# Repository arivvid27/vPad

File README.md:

# vPad

### Note:
> This is probably something I'm
> gonna reiterate on a lot
> whenever I have time, so, it's a
> WIP

## Current Features:
- Mechanical Switches (MX Basic | Macros)
- Two NeoPixels (Ambience)
- Encoder + Switch (Volume/Brightness Control/Mute/Unmute/More Macros)

## What's Holding it Together;
- Not Duct-Tape this time
- KMK Firmware
- Circuit Python

## WIP Stuff:
- Custom Software to work with this pad
- Mini OLED Screen
- Better Ambient Lighting (Underglow, Keycaps)

## Future Stuff:
- Expand to full Keyboards
- Mice?
- Definitely a Better case 😭
- More Switches (Imma find those push things where they stay on until you push them again)

## Challenges:
I was quite a bit stumped on how to use KiCad. The tutorial helped a ton. I also have never imported anything into F360... so it took me a while to figure that out.
Overall, I think I learned a lot from this, and I will continue to make PCBs now that I know how to. :)

## Schematics:

## PCB:

## (Attempt at) Case:

## BOM
- 2x SK6812MINI
- 4x Cherry MX Standard Switches (Anything Tactile)
- 1x EC11 Rotary Encoder
- 1x XIAO RP2040 DIP

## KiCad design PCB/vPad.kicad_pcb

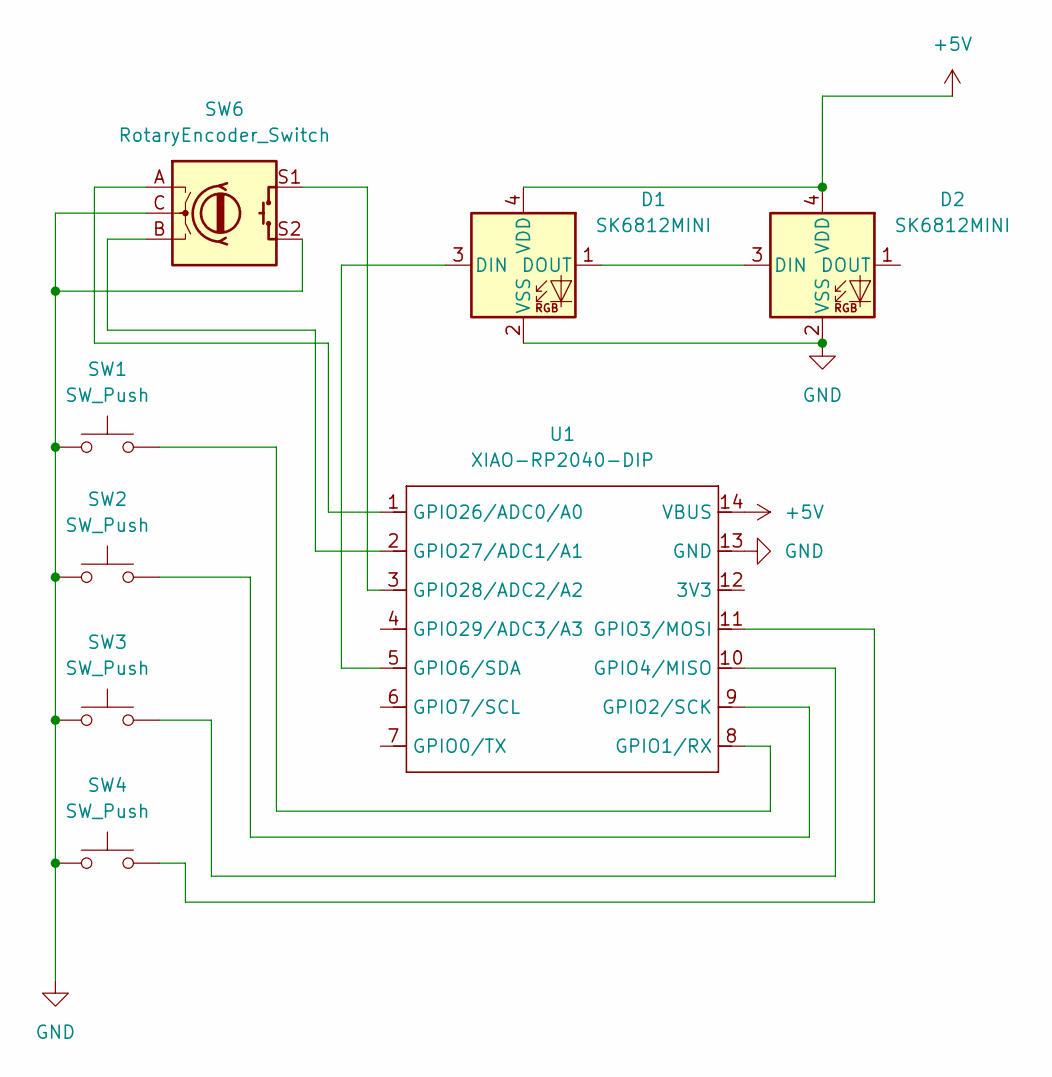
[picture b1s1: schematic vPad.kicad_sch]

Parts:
D1, D2: SK6812MINI; LED_SK6812MINI_PLCC4_3.5x3.5mm_P1.75mm
SW1, SW2, SW3, SW4: SW_Push; Kailh-PG1353-Solderable-1.5U
SW6: RotaryEncoder_Switch; RotaryEncoder_Alps_EC11E-Switch_Vertical_H20mm
U1: XIAO-RP2040-DIP

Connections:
+5V: D1.4 (VDD), D2.4 (VDD), U1.14 (VBUS)
GND: D1.2 (VSS), D2.2 (VSS), SW1.1, SW2.1, SW3.1, SW4.1, SW6.C, SW6.S2, U1.13 (GND)
unnamed: D1.3 (DIN), U1.5 (GPIO6/SDA)
unnamed: D1.1 (DOUT), D2.3 (DIN)
unnamed: SW1.2, U1.8 (GPIO1/RX)
unnamed: SW2.2, U1.9 (GPIO2/SCK)
unnamed: SW4.2, U1.11 (GPIO3/MOSI)
unnamed: SW3.2, U1.10 (GPIO4/MISO)
unnamed: SW6.A, U1.1 (GPIO26/ADC0/A0)
unnamed: SW6.B, U1.2 (GPIO27/ADC1/A1)
unnamed: SW6.S1, U1.3 (GPIO28/ADC2/A2)

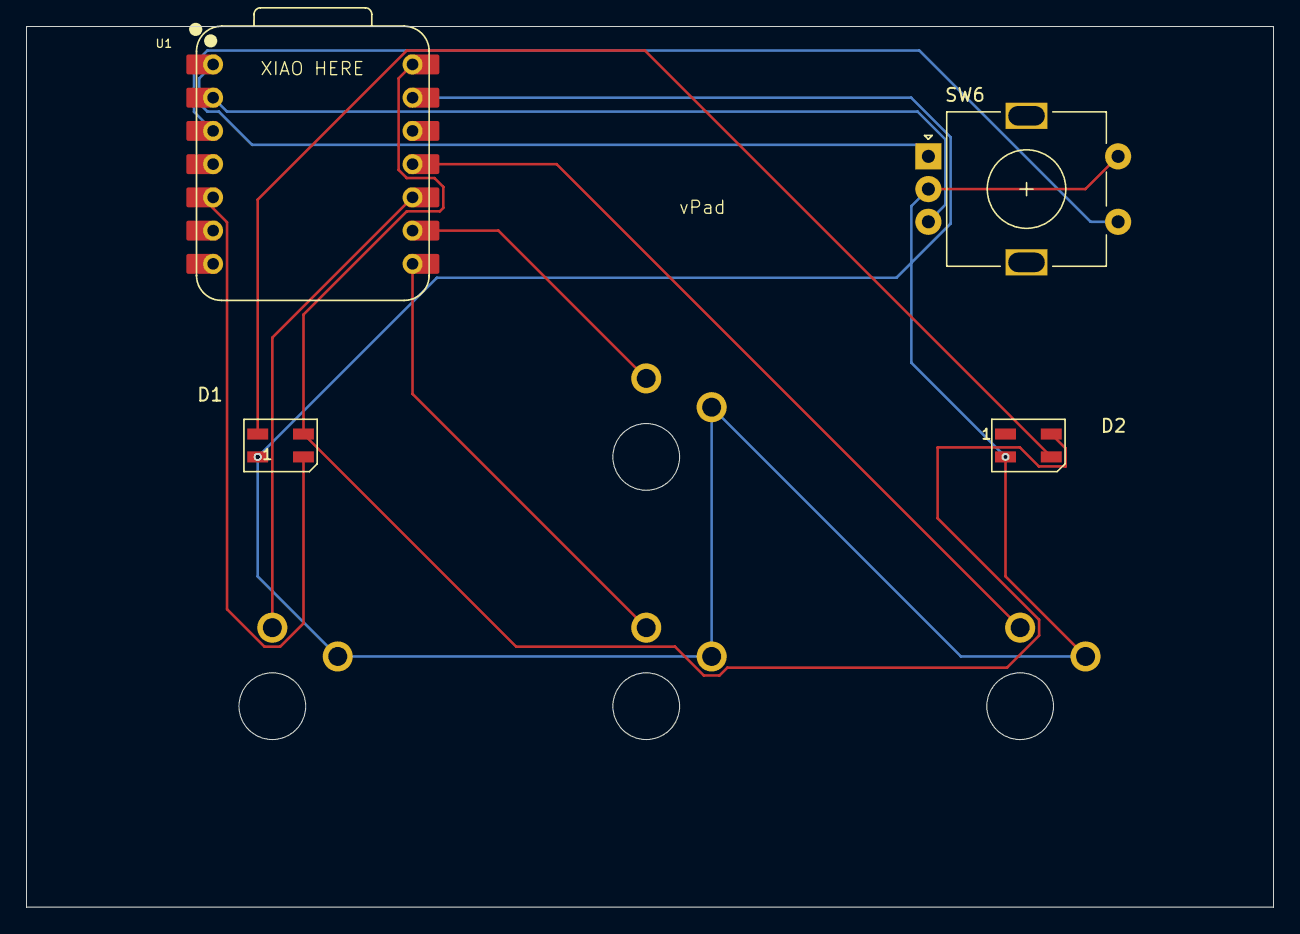
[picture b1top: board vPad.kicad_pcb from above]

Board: 2 copper layers, 95.3 x 67.3 mm, 8 parts (0 on the bottom side), 11 nets.

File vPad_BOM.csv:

"Reference","Qty","Value","DNP","Exclude from BOM","Exclude from Board","Footprint","Datasheet"
"D1,D2","2","SK6812MINI","","","","LED_SMD:LED_SK6812MINI_PLCC4_3.5x3.5mm_P1.75mm","https://cdn-shop.adafruit.com/product-files/2686/SK6812MINI_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"
"SW1,SW2,SW3,SW4","4","SW_Push","","","","Kailh_PG1353_Solderable:Kailh-PG1353-Solderable-1.5U","~"
"SW6","1","RotaryEncoder_Switch","","","","Rotary_Encoder:RotaryEncoder_Alps_EC11E-Switch_Vertical_H20mm","~"
"U1","1","XIAO-RP2040-DIP","","","","Seeed Studio XIAO Series Library:XIAO-RP2040-DIP",""

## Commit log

2025-11-11 Finished CAD and PCB; Will Work on Firmware (Proto)
2025-11-11 Took Firmware from Tutorial. Will Update once can test on it.
2025-11-12 updated my stuff
